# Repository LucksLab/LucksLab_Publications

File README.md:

# LucksLab_Publications
Code and accessory files related to publications from the Lucks Lab. More information about Lucks Lab publications can be found at http://luckslab.org/publications/, and more information about the Lucks Lab at http://luckslab.org/ .

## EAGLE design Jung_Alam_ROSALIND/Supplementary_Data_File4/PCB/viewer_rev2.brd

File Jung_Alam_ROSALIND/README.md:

# "Cell-free biosensors for rapid detection of water contaminants"
Jung, Alam et al. (2020)

---

## Supplementary Data Files
Below are the descriptions of the supplementary data files for the manuscript. These files are available at "LINKTBD."

| File | Description |
| ---: | :----------- |
| Video 1 | Illumination of an unregulated ROSALIND reaction |
| Video 2 | Freeze-drying and packaging of ROSALIND reactions |
| Data File 1 | Raw illuminator and freeze-dried packaging method images included in figures |
| Data File 2 | Template excel worksheet for setting up a ROSALIND reaction |
| Data File 3 | Calibrated plate reader data for all figures |
| Data File 5 | DNA and Protein sequences used in this study |

The following data is included in this GitHub repository:

| File | Description |
| ---: | :----------- |
| Data File 4 | Instructions for 3D printing and assembling a hand-held illuminator (includes 3D print and CAD files for the illuminator + EPF and gbr files for the printed circuit board. |

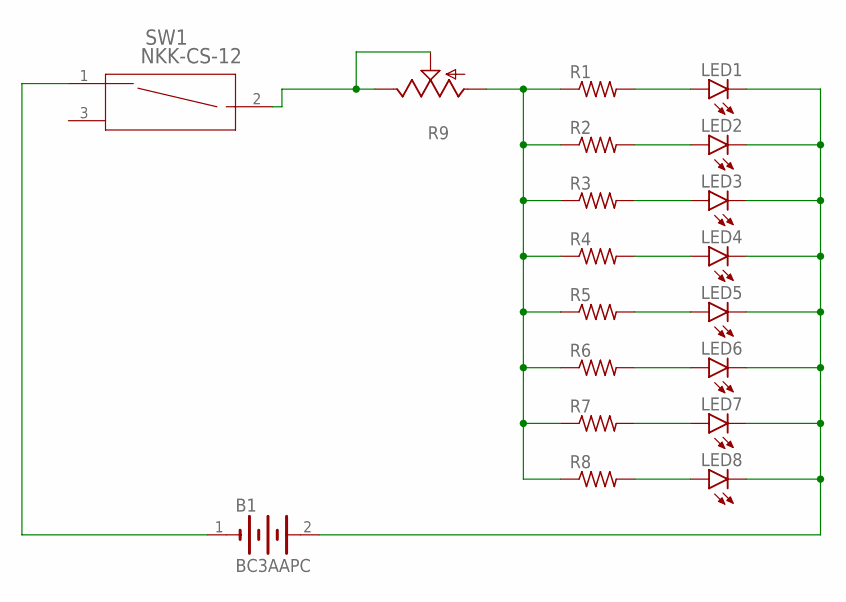
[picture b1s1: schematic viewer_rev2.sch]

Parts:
B1: BC3AAPC; BC3AAAPC
LED1, LED2, LED3, LED4, LED5, LED6, LED7, LED8: LED5MM
R1, R2, R3, R4, R5, R6, R7, R8: R-US_VMTB60; VMTB60
R9: TRIM_US-CT6; CT6
SW1: NKK-CS-12; SW3-SLIDE-2POL_P185

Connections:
unnamed: B1.1 (-), SW1.1
unnamed: R1.1, R2.1, R3.1, R4.1, R5.1, R6.1, R7.1, R8.1, R9.A
unnamed: R9.E, R9.S, SW1.2 (3)
unnamed: LED8.A, R8.2
unnamed: LED7.A, R7.2
unnamed: LED6.A, R6.2
unnamed: LED5.A, R5.2
unnamed: LED4.A, R4.2
unnamed: LED3.A, R3.2
unnamed: LED2.A, R2.2
unnamed: LED1.A, R1.2
unnamed: B1.2 (+), LED1.K (C), LED2.K (C), LED3.K (C), LED4.K (C), LED5.K (C), LED6.K (C), LED7.K (C), LED8.K (C)

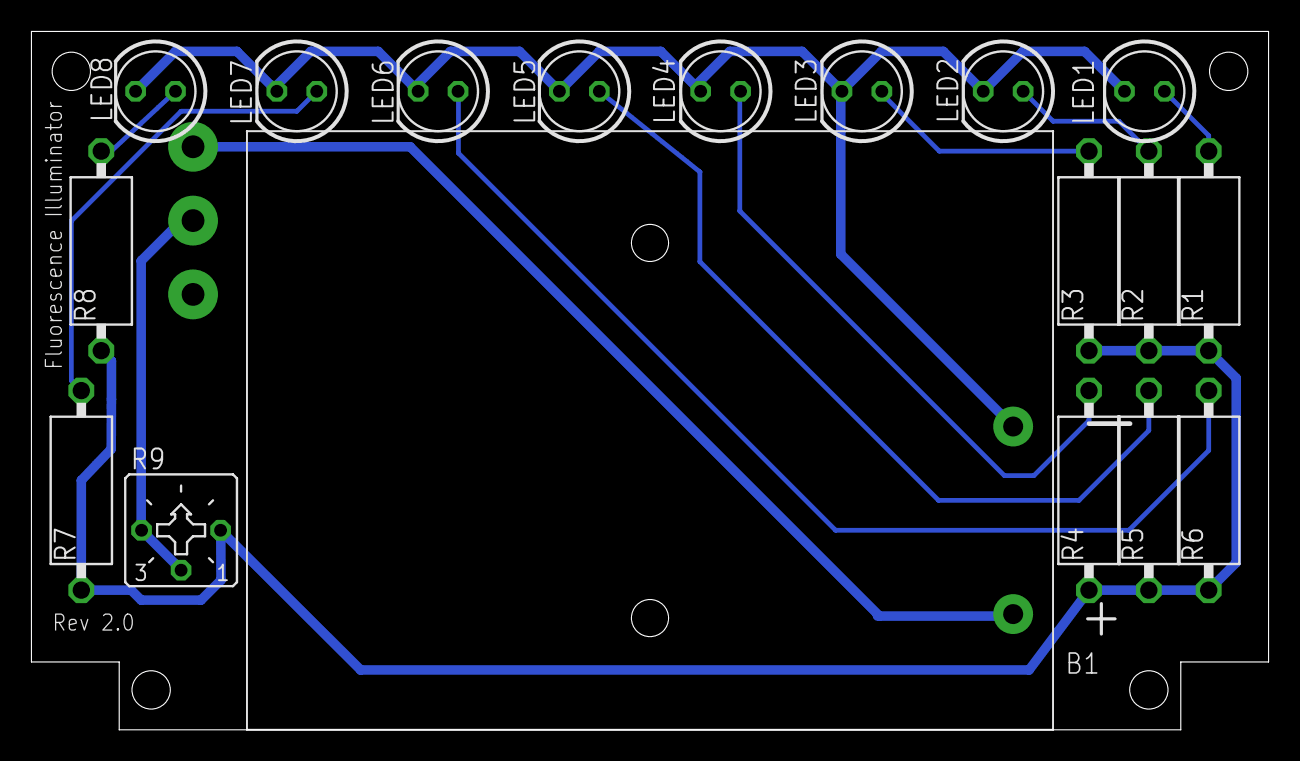
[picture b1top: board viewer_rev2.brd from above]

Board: 2 copper layers, 78.7 x 44.5 mm, 19 parts (1 on the bottom side), 12 nets.

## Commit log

2017-12-06 Initial commit of files for Hu_Takahashi_sRNA_Negative_Autoregulation/
2017-12-06 Readme updates
2017-12-20 Script for 'Probing of RNA structures in a positive sense RNA virus reveals selection pressures for structural elements' Nucleic Acids Research
2017-12-20 Changing directory name of Watters_CMV_RNA_Structures
2019-01-15 Files for computational analysis of ZTP riboswitch mutagenesis experiments
2019-03-04 Added assessment code
2019-10-01 Added shuffle randomization
2020-04-30 Directory Creation
2020-04-30 Adding new Readme and illuminator files
2020-04-30 README change
2020-05-01 Added PCB Files
2021-01-28 Initial Folder creation
